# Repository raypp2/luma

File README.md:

# Luma LED Pendant

<u>Overview</u> &nbsp;&nbsp;&nbsp;|&nbsp;&nbsp;&nbsp; [🧭 Laser Cutting](./documentation/laser.md) &nbsp;&nbsp;&nbsp;|&nbsp;&nbsp;&nbsp; [🛠️ 3D Printing](./documentation/3dmodel.md) &nbsp;&nbsp;&nbsp;|&nbsp;&nbsp;&nbsp; [🔮 Roadmap](./documentation/roadmap.md)

*This is a short description*

**Technical Notes**:
- Bullet 1
- Bullet 2

## 🙋‍♂️ Who is this for

Something about who this is for, what it does, and why it is useful.

## TODO

[] Apply google analytics
[] Write basic documentation on Github
[] Update team to instagram tags

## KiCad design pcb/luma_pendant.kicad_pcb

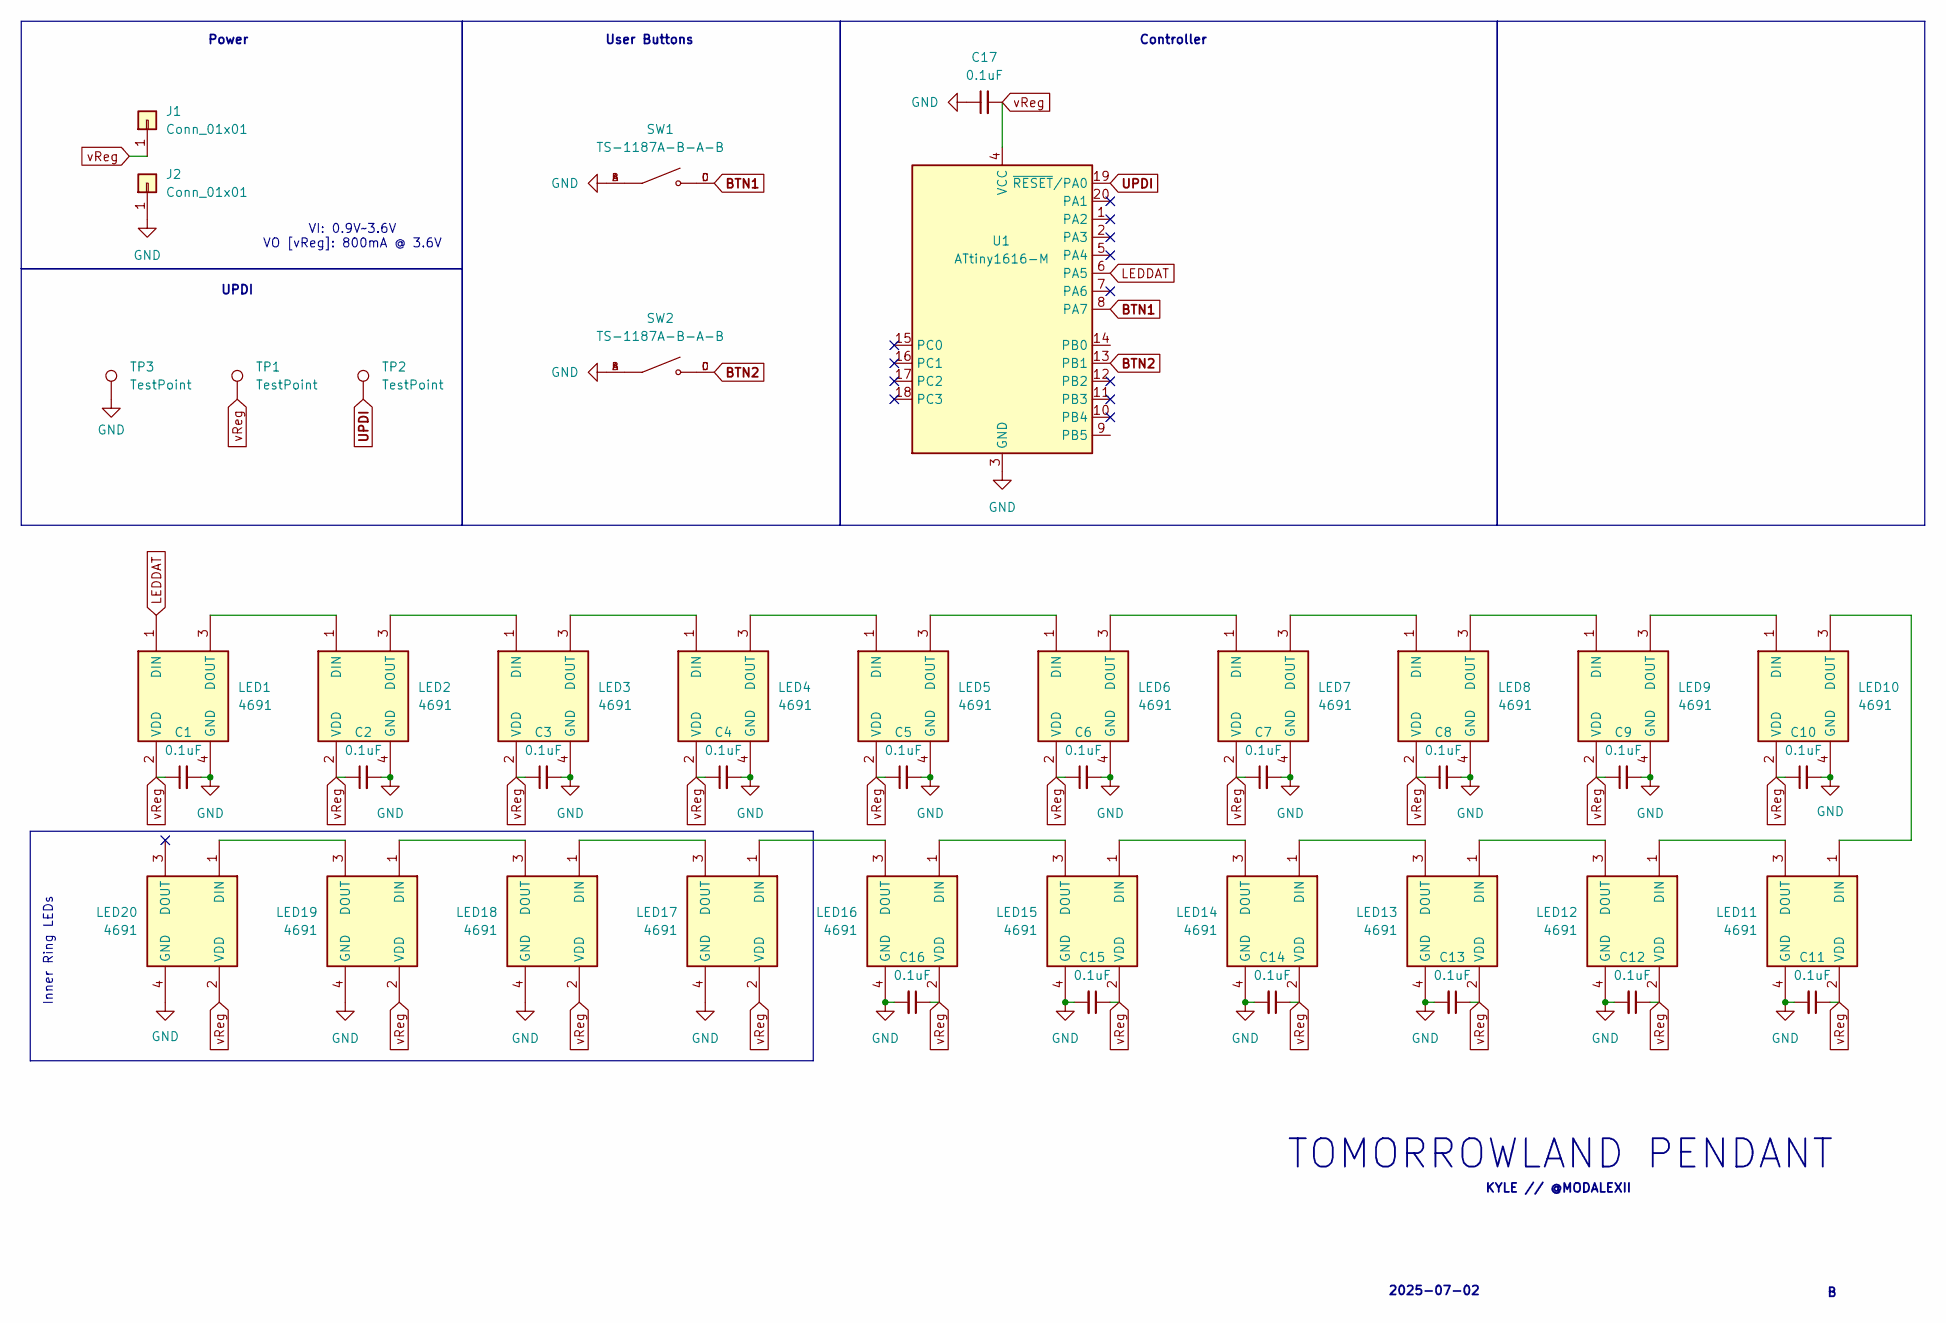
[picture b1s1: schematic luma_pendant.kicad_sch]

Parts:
C1, C2, C3, C4, C5, C6, C7, C8, C9, C10, C11, C12, C13, C14, C15, C16, C17: 0.1uF; C_0402_1005Metric
J1: Conn_01x01; TestPoint_THTPad_2.0x2.0mm_Drill1.0mm
J2: Conn_01x01; TestPoint_THTPad_D2.0mm_Drill1.0mm
LED1, LED2, LED3, LED4, LED5, LED6, LED7, LED8, LED9, LED10, LED11, LED12, LED13, LED14, LED15, LED16, LED17, LED18, LED19, LED20: 4691; Mouser Part Number 485-4691
SW1, SW2: TS-1187A-B-A-B; SW_TS-1187A-B-A-B; PARTREV A0
TP1, TP2, TP3: TestPoint; TestPoint_THTPad_D1.5mm_Drill0.7mm
U1: ATtiny1616-M; VQFN-20-1EP_3x3mm_P0.4mm_EP1.7x1.7mm

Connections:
BTN1: SW1.C, SW1.D, U1.8 (PA7)
BTN2: SW2.C, SW2.D, U1.13 (PB1)
GND: C1.2, C2.2, C3.2, C4.2, C5.2, C6.2, C7.2, C8.2, C9.2, C10.2, C11.2, C12.2, C13.2, C14.2, C15.2, C16.2, C17.1, J2.1, LED1.4 (GND), LED2.4 (GND), LED3.4 (GND), LED4.4 (GND), LED5.4 (GND), LED6.4 (GND), LED7.4 (GND), LED8.4 (GND), LED9.4 (GND), LED10.4 (GND), LED11.4 (GND), LED12.4 (GND), LED13.4 (GND), LED14.4 (GND), LED15.4 (GND), LED16.4 (GND), LED17.4 (GND), LED18.4 (GND), LED19.4 (GND), LED20.4 (GND), SW1.A, SW1.B, SW2.A, SW2.B, TP3.1, U1.3 (GND), U1.21 (GND)
LEDDAT: LED1.1 (DIN), U1.6 (PA5)
unnamed: LED1.3 (DOUT), LED2.1 (DIN)
unnamed: LED2.3 (DOUT), LED3.1 (DIN)
unnamed: LED3.3 (DOUT), LED4.1 (DIN)
unnamed: LED4.3 (DOUT), LED5.1 (DIN)
unnamed: LED5.3 (DOUT), LED6.1 (DIN)
unnamed: LED6.3 (DOUT), LED7.1 (DIN)
unnamed: LED7.3 (DOUT), LED8.1 (DIN)
unnamed: LED8.3 (DOUT), LED9.1 (DIN)
unnamed: LED9.3 (DOUT), LED10.1 (DIN)
unnamed: LED10.3 (DOUT), LED11.1 (DIN)
unnamed: LED11.3 (DOUT), LED12.1 (DIN)
unnamed: LED12.3 (DOUT), LED13.1 (DIN)
unnamed: LED13.3 (DOUT), LED14.1 (DIN)
unnamed: LED14.3 (DOUT), LED15.1 (DIN)
unnamed: LED15.3 (DOUT), LED16.1 (DIN)
unnamed: LED16.3 (DOUT), LED17.1 (DIN)
unnamed: LED17.3 (DOUT), LED18.1 (DIN)
unnamed: LED18.3 (DOUT), LED19.1 (DIN)
unnamed: LED19.3 (DOUT), LED20.1 (DIN)
UPDI: TP2.1, U1.19 (~RESET/PA0)
vReg: C1.1, C2.1, C3.1, C4.1, C5.1, C6.1, C7.1, C8.1, C9.1, C10.1, C11.1, C12.1, C13.1, C14.1, C15.1, C16.1, C17.2, J1.1, LED1.2 (VDD), LED2.2 (VDD), LED3.2 (VDD), LED4.2 (VDD), LED5.2 (VDD), LED6.2 (VDD), LED7.2 (VDD), LED8.2 (VDD), LED9.2 (VDD), LED10.2 (VDD), LED11.2 (VDD), LED12.2 (VDD), LED13.2 (VDD), LED14.2 (VDD), LED15.2 (VDD), LED16.2 (VDD), LED17.2 (VDD), LED18.2 (VDD), LED19.2 (VDD), LED20.2 (VDD), TP1.1, U1.4 (VCC)

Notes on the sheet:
2025-07-02
VI: 0.9V~3.6V VO [vReg]: 800mA @ 3.6V
Controller
Inner Ring LEDs
KYLE // @MODALEXII
Power
TOMORROWLAND PENDANT
UPDI
User Buttons

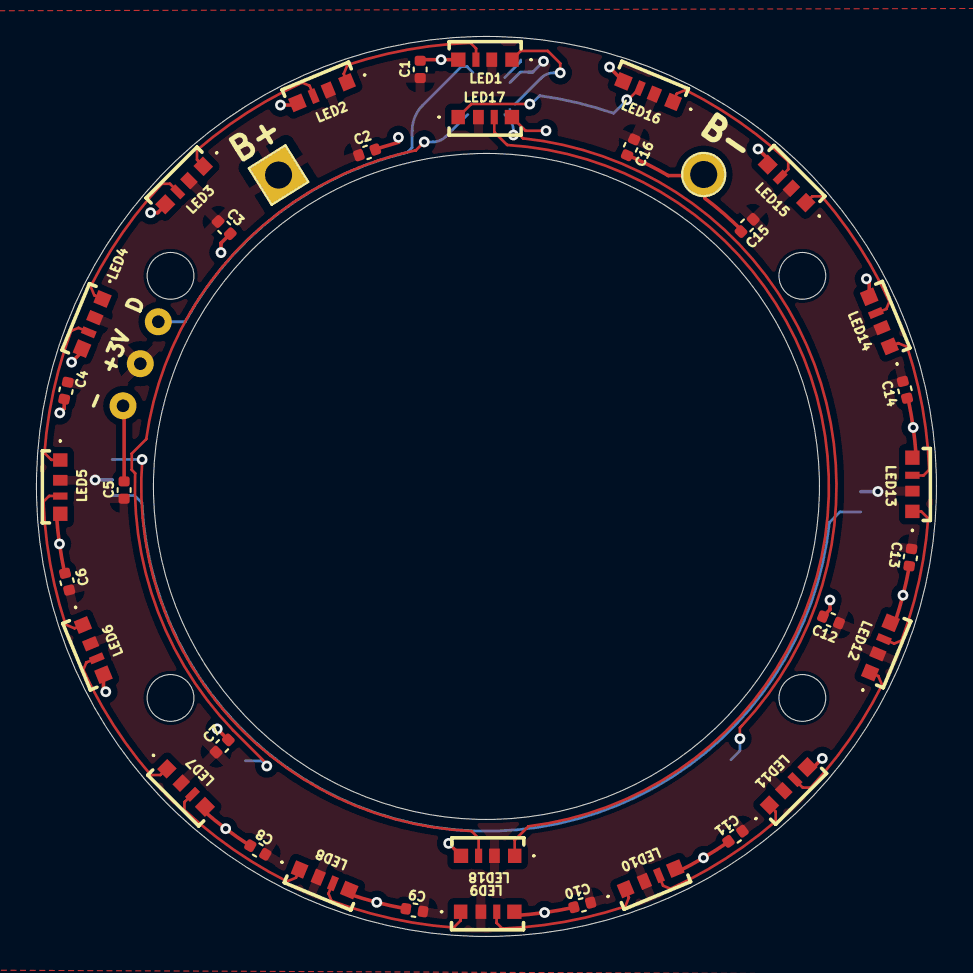
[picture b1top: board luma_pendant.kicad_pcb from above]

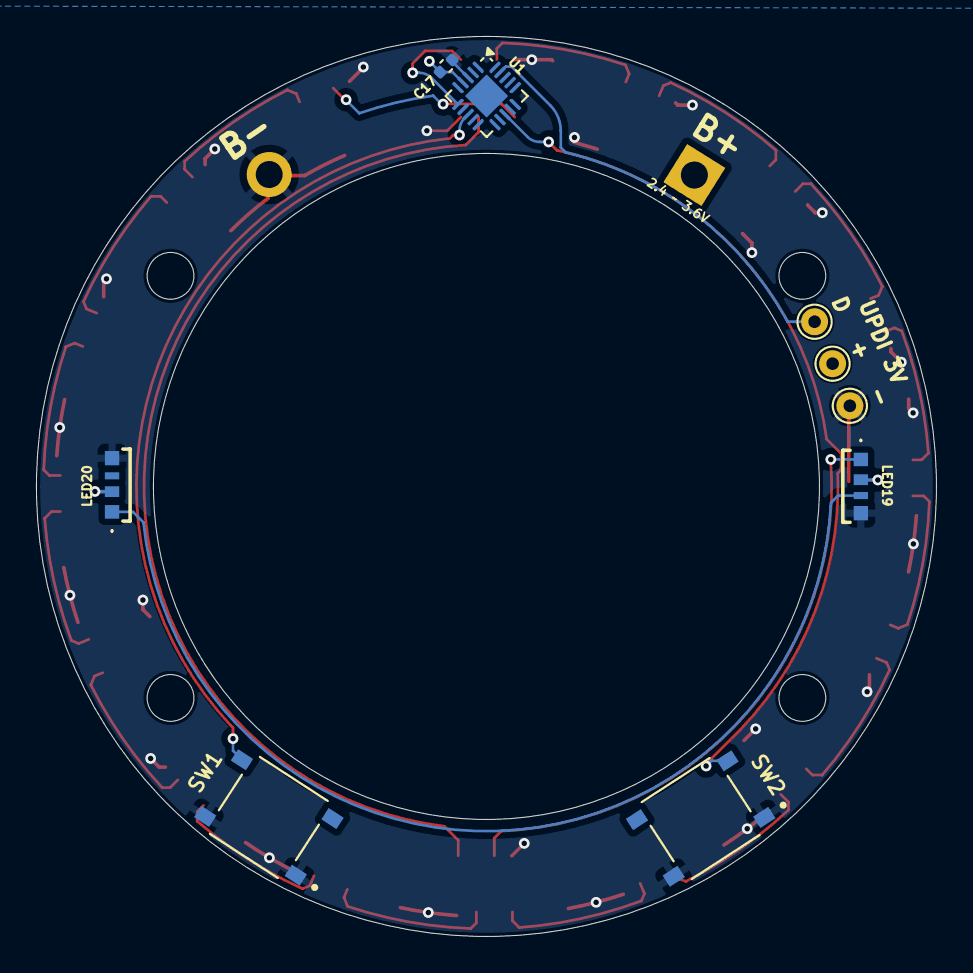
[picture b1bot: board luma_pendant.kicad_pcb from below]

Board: 2 copper layers, 50.0 x 50.0 mm, 45 parts (9 on the bottom side), 25 nets.

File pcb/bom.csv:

"Comment","Designator","Footprint","LCSC Part Number"
"0.1uF","C1,C2,C3,C4,C5,C6,C7,C8,C9,C10,C11,C12,C13,C14,C15,C16,C17","0402","C1525"
"SK6812SIDE-A-S Side edmit addressible LED","LED18,LED11,LED17,LED3,LED10,LED9,LED13,LED8,LED6,LED16,LED2,LED12,LED7,LED5,LED14,LED4,LED1,LED15,LED19,LED20","SMD-4P,4x1.6mm","C5378737"
"TS-1187A-C-J-B 5.1mm momentary button 5mm plunger","SW1,SW2","SMD","C318885"
"ATtiny1616-M","U1","QFN-20-EP","C507118"

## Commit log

2025-07-13 documentation template
2025-07-13 documentation templates
2025-07-14 Inner light patterns
2025-07-14 added inner light patterns
2025-07-15 Merging local commits with repo. Patterns now save via the EEPROM and code has been refactored to support this
2025-07-15 Mapping brightness to button2 and saving the state to the EEPROM
2025-07-15 Trotek Laser Print Ready Files
2025-07-15 Added outerCycle() and innerCycle()
2025-07-16 update laser cut files
2025-07-17 Added inner patterns
2025-07-17 adding changes addressing excessive brightness
2025-07-18 Adjustments after pilot wear
